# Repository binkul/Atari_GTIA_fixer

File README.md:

# Fully working fixer for faulty Atari GTIA
source: http://atariki.krap.pl/index.php/Simius_GTIA_Fixer
picture of ready PCB from JLCPCB: https://drive.google.com/file/d/12akioqNmc9vnPLK2LAhbNn0Du7kyHStm/view?usp=sharing

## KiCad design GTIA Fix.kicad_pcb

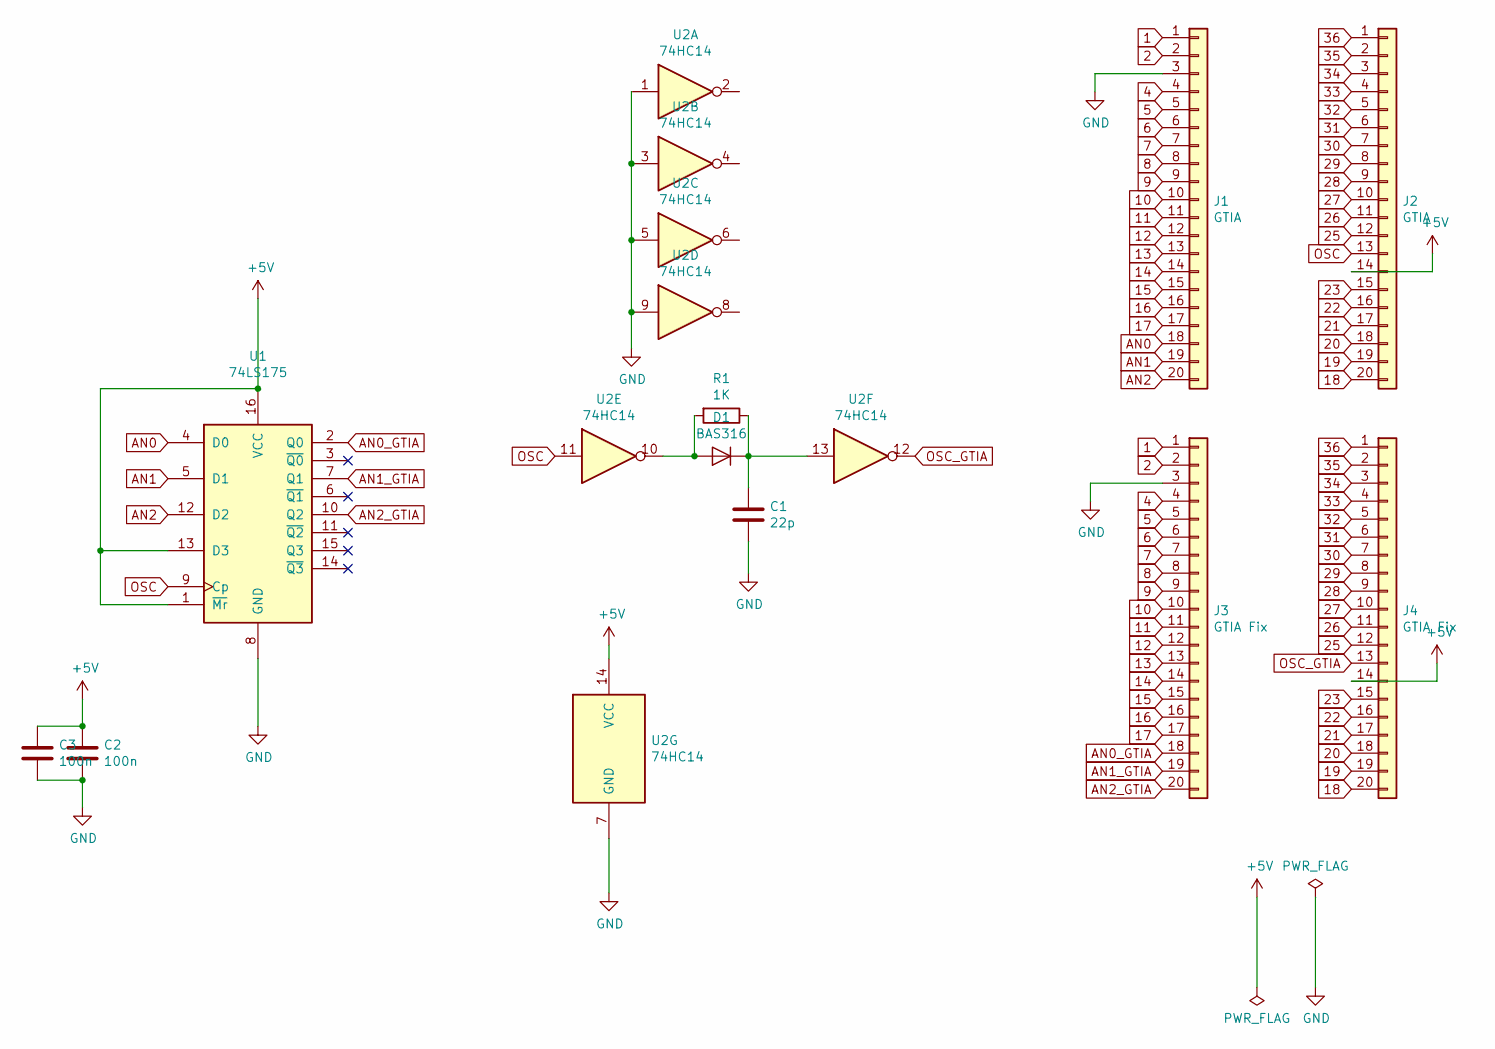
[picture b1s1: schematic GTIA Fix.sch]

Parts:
C1: 22p; R_1206_3216Metric
C2, C3: 100n; R_1206_3216Metric
D1: BAS316; Diode_SOD-523_HandSoldering
J1, J2: GTIA; PinHeader_1x20_P2.54mm_Vertical
J3, J4: GTIA Fix; PinHeader_1x20_P2.54mm_Vertical
R1: 1K; R_1206_3216Metric
U1: 74LS175; SOIC-16_3.9x9.9mm_P1.27mm
U2: 74HC14; SOIC-14_3.9x8.7mm_P1.27mm

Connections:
1: J1.1, J3.1
2: J1.2, J3.2
4: J1.4, J3.4
5: J1.5, J3.5
6: J1.6, J3.6
7: J1.7, J3.7
8: J1.8, J3.8
9: J1.9, J3.9
10: J1.10, J3.10
11: J1.11, J3.11
12: J1.12, J3.12
13: J1.13, J3.13
14: J1.14, J3.14
15: J1.15, J3.15
16: J1.16, J3.16
17: J1.17, J3.17
18: J2.20, J4.20
19: J2.19, J4.19
20: J2.18, J4.18
21: J2.17, J4.17
22: J2.16, J4.16
23: J2.15, J4.15
25: J2.12, J4.12
26: J2.11, J4.11
27: J2.10, J4.10
28: J2.9, J4.9
29: J2.8, J4.8
30: J2.7, J4.7
31: J2.6, J4.6
32: J2.5, J4.5
33: J2.4, J4.4
34: J2.3, J4.3
35: J2.2, J4.2
36: J2.1, J4.1
+5V: C2.1, C3.1, J2.14, J4.14, U1.1 (~Mr), U1.13 (D3), U1.16 (VCC), U2.14 (VCC)
AN0: J1.18, U1.4 (D0)
AN0_GTIA: J3.18, U1.2 (Q0)
AN1: J1.19, U1.5 (D1)
AN1_GTIA: J3.19, U1.7 (Q1)
AN2: J1.20, U1.12 (D2)
AN2_GTIA: J3.20, U1.10 (Q2)
GND: C1.2, C2.2, C3.2, J1.3, J3.3, U1.8 (GND), U2.1, U2.3, U2.5, U2.7 (GND), U2.9
unnamed: C1.1, D1.1 (K), R1.1, U2.13
unnamed: D1.2 (A), R1.2, U2.10
OSC: J2.13, U1.9 (Cp), U2.11
OSC_GTIA: J4.13, U2.12

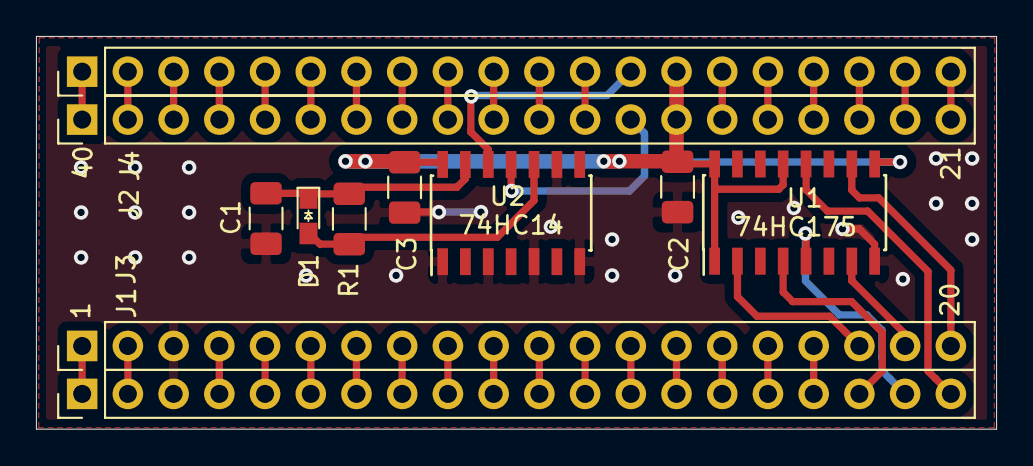
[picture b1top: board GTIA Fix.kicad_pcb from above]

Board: 2 copper layers, 53.3 x 21.8 mm, 11 parts (0 on the bottom side), 46 nets.

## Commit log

2020-11-07 Full diagram and PCB
2021-01-17 modification
